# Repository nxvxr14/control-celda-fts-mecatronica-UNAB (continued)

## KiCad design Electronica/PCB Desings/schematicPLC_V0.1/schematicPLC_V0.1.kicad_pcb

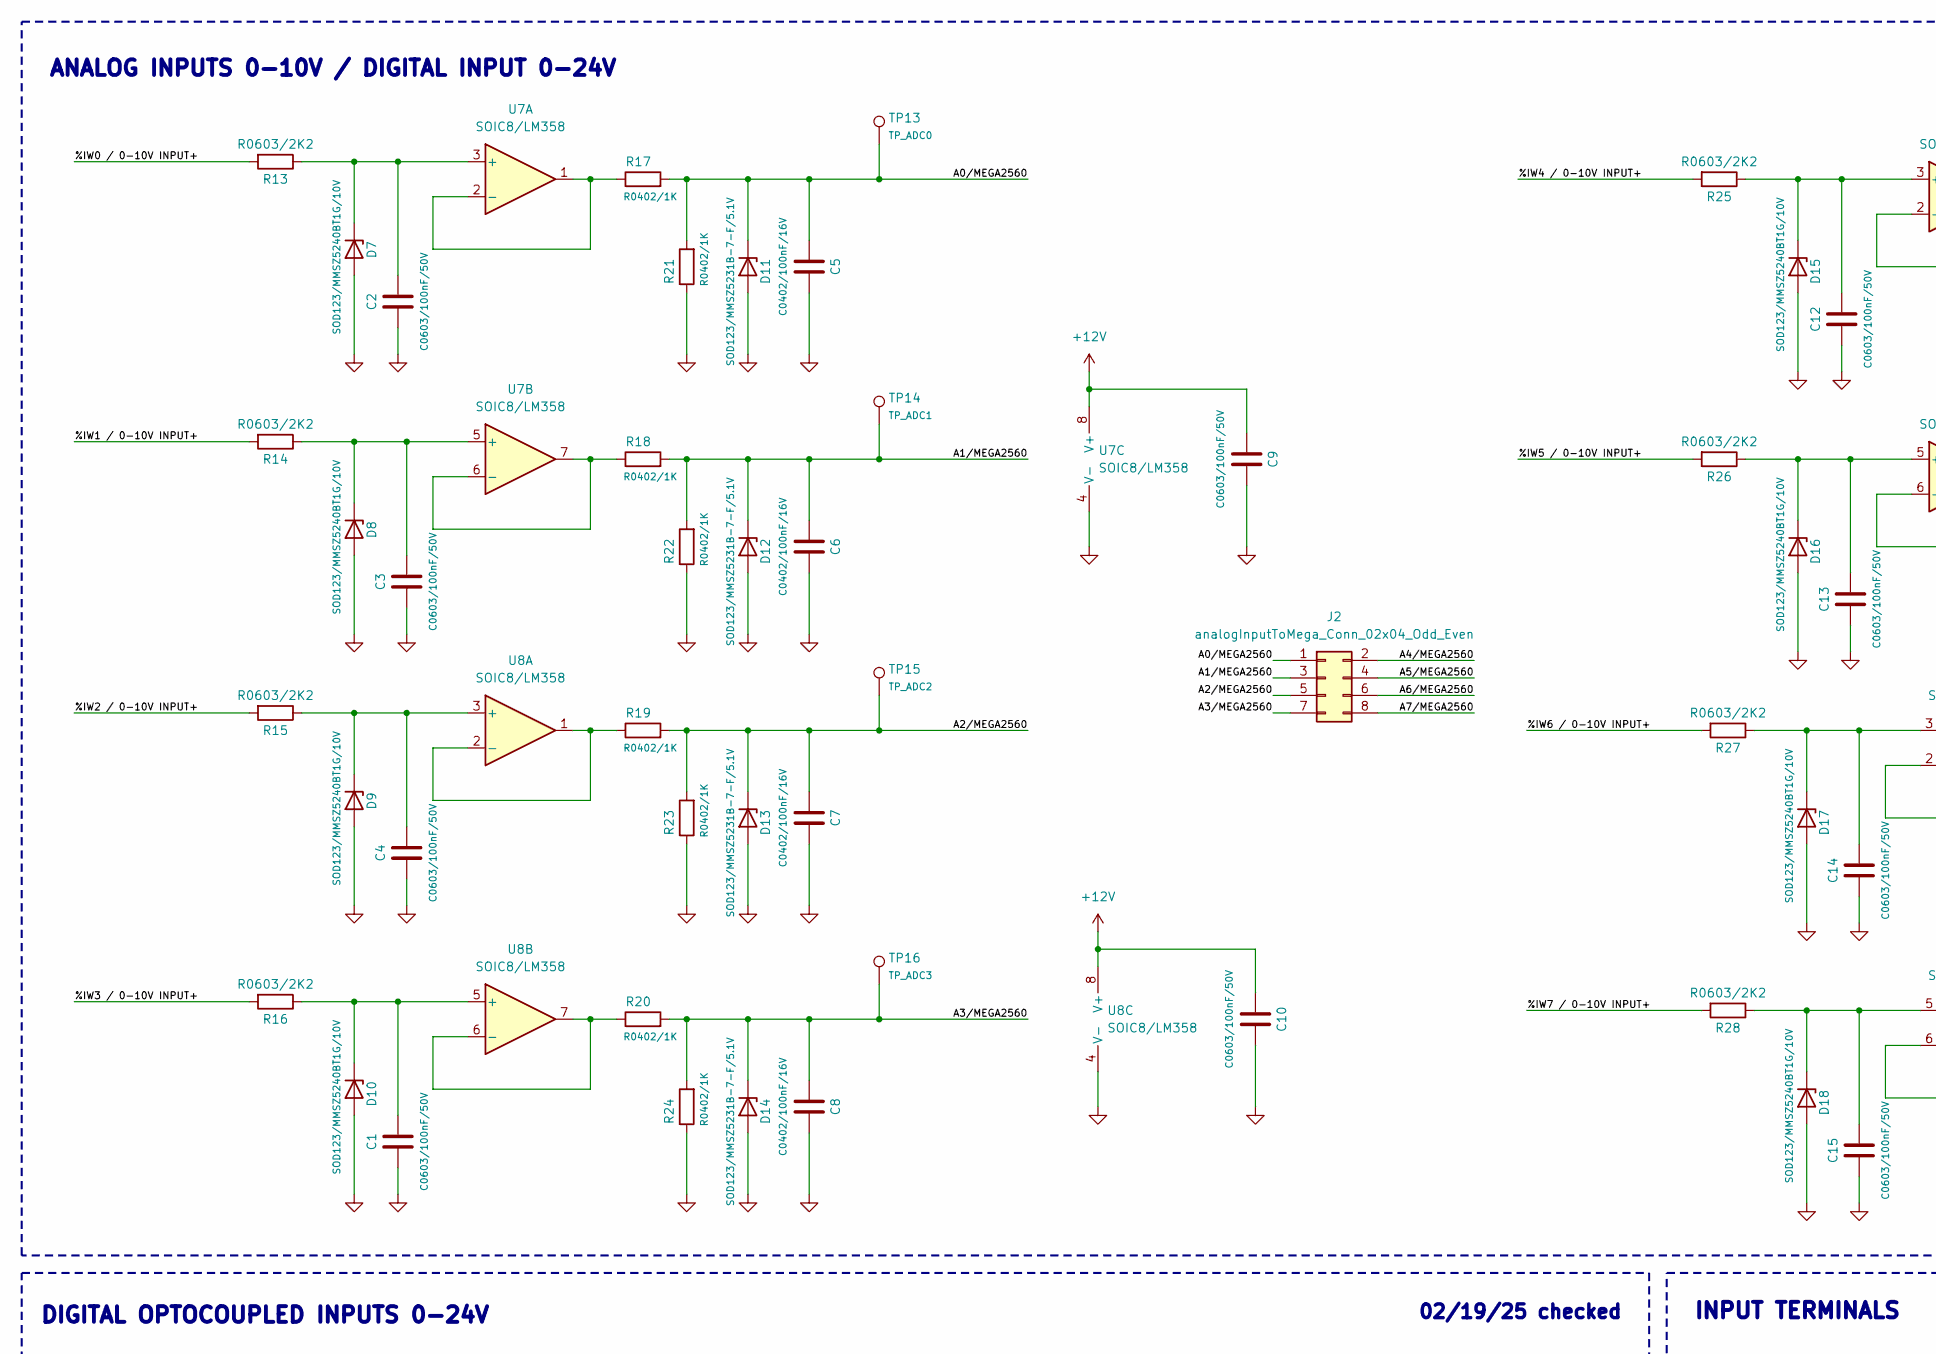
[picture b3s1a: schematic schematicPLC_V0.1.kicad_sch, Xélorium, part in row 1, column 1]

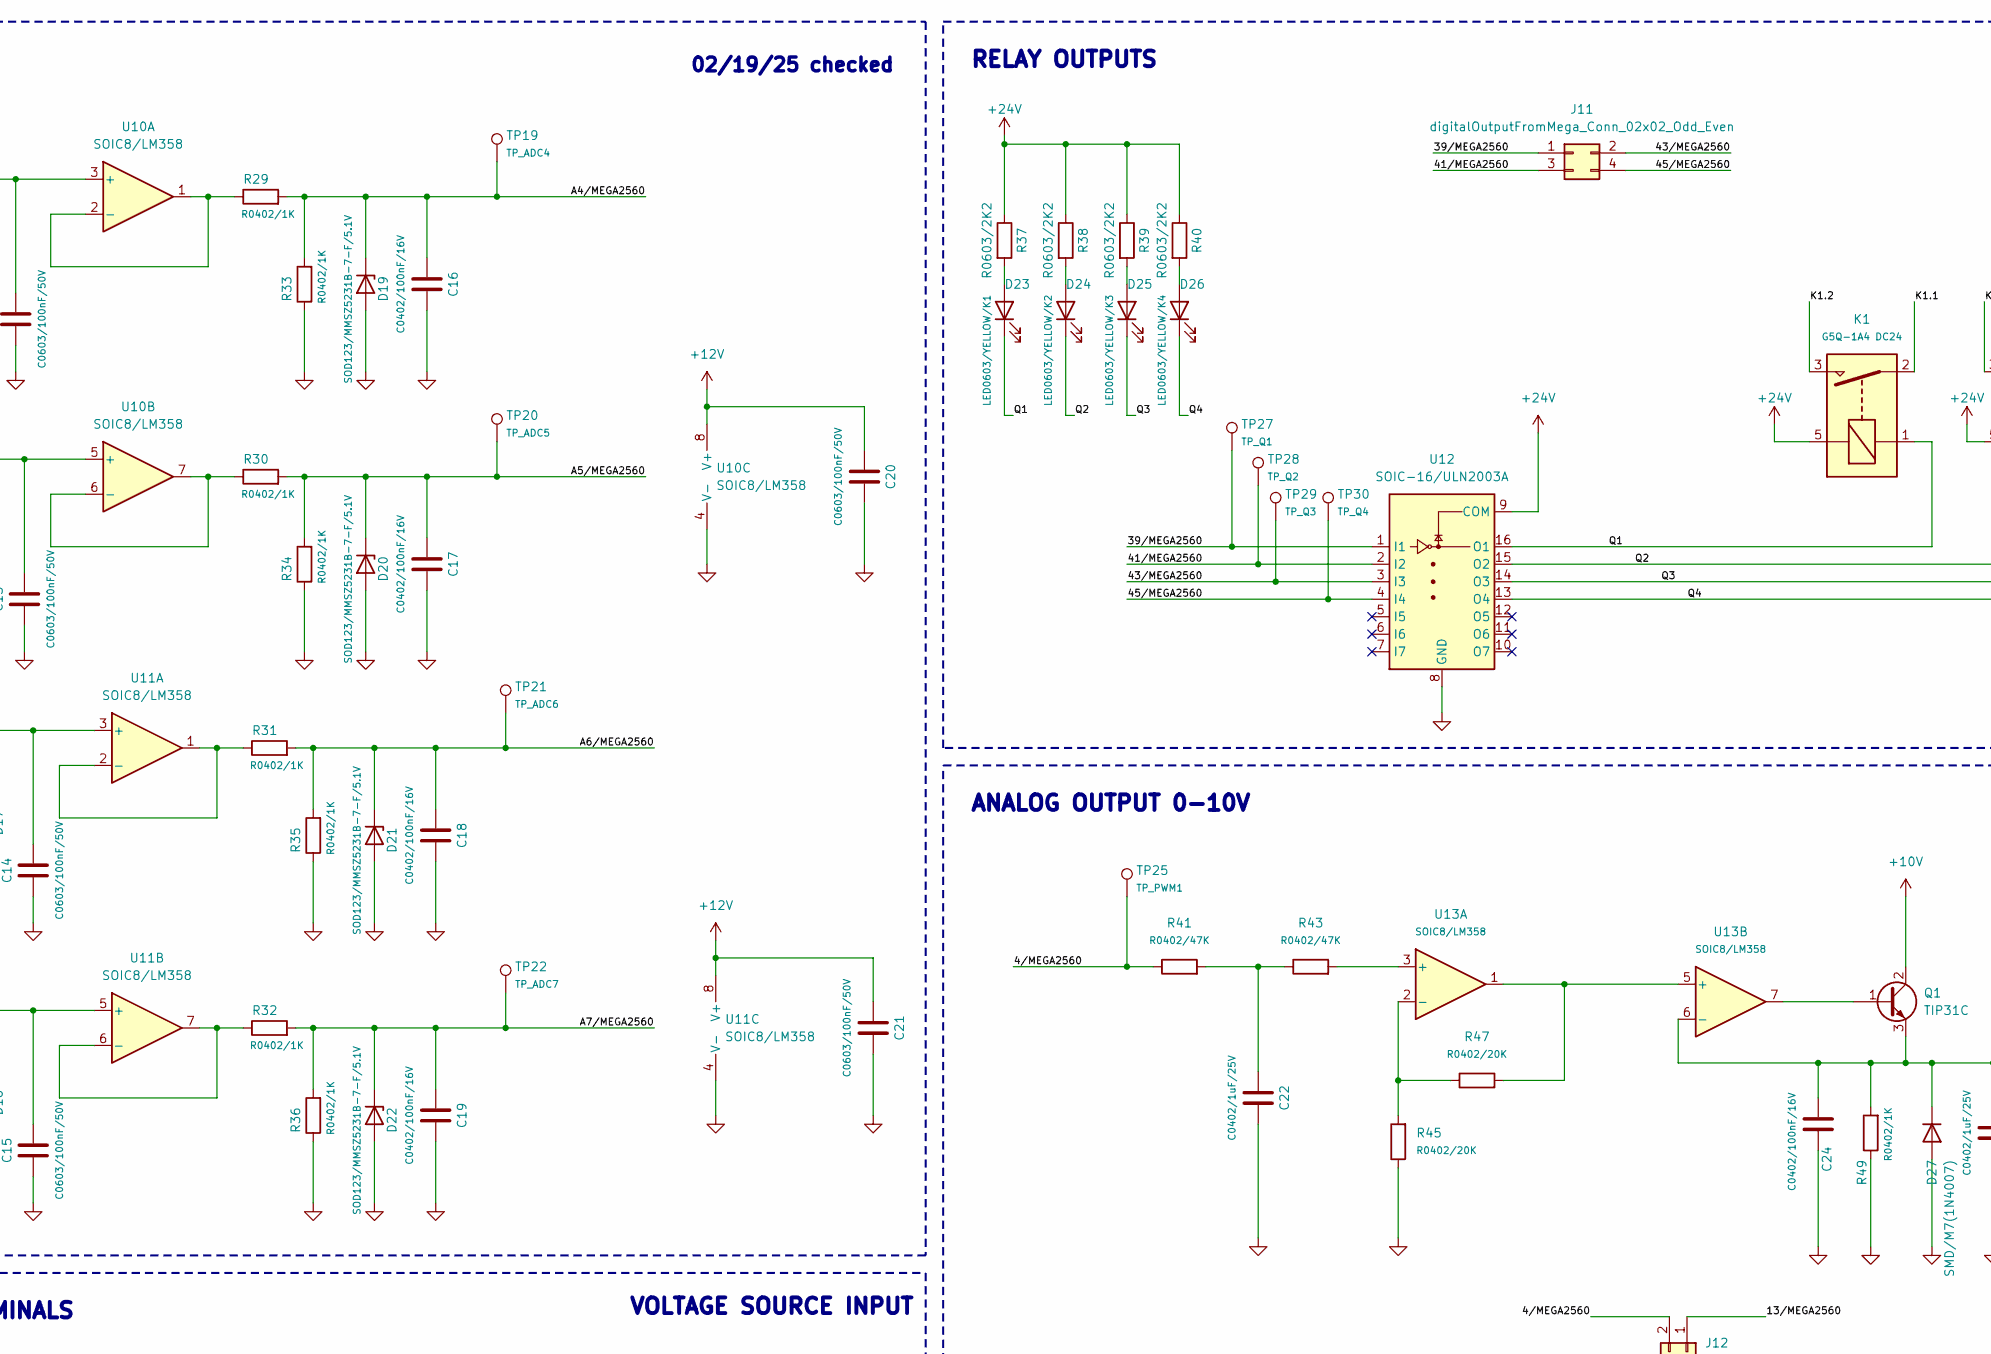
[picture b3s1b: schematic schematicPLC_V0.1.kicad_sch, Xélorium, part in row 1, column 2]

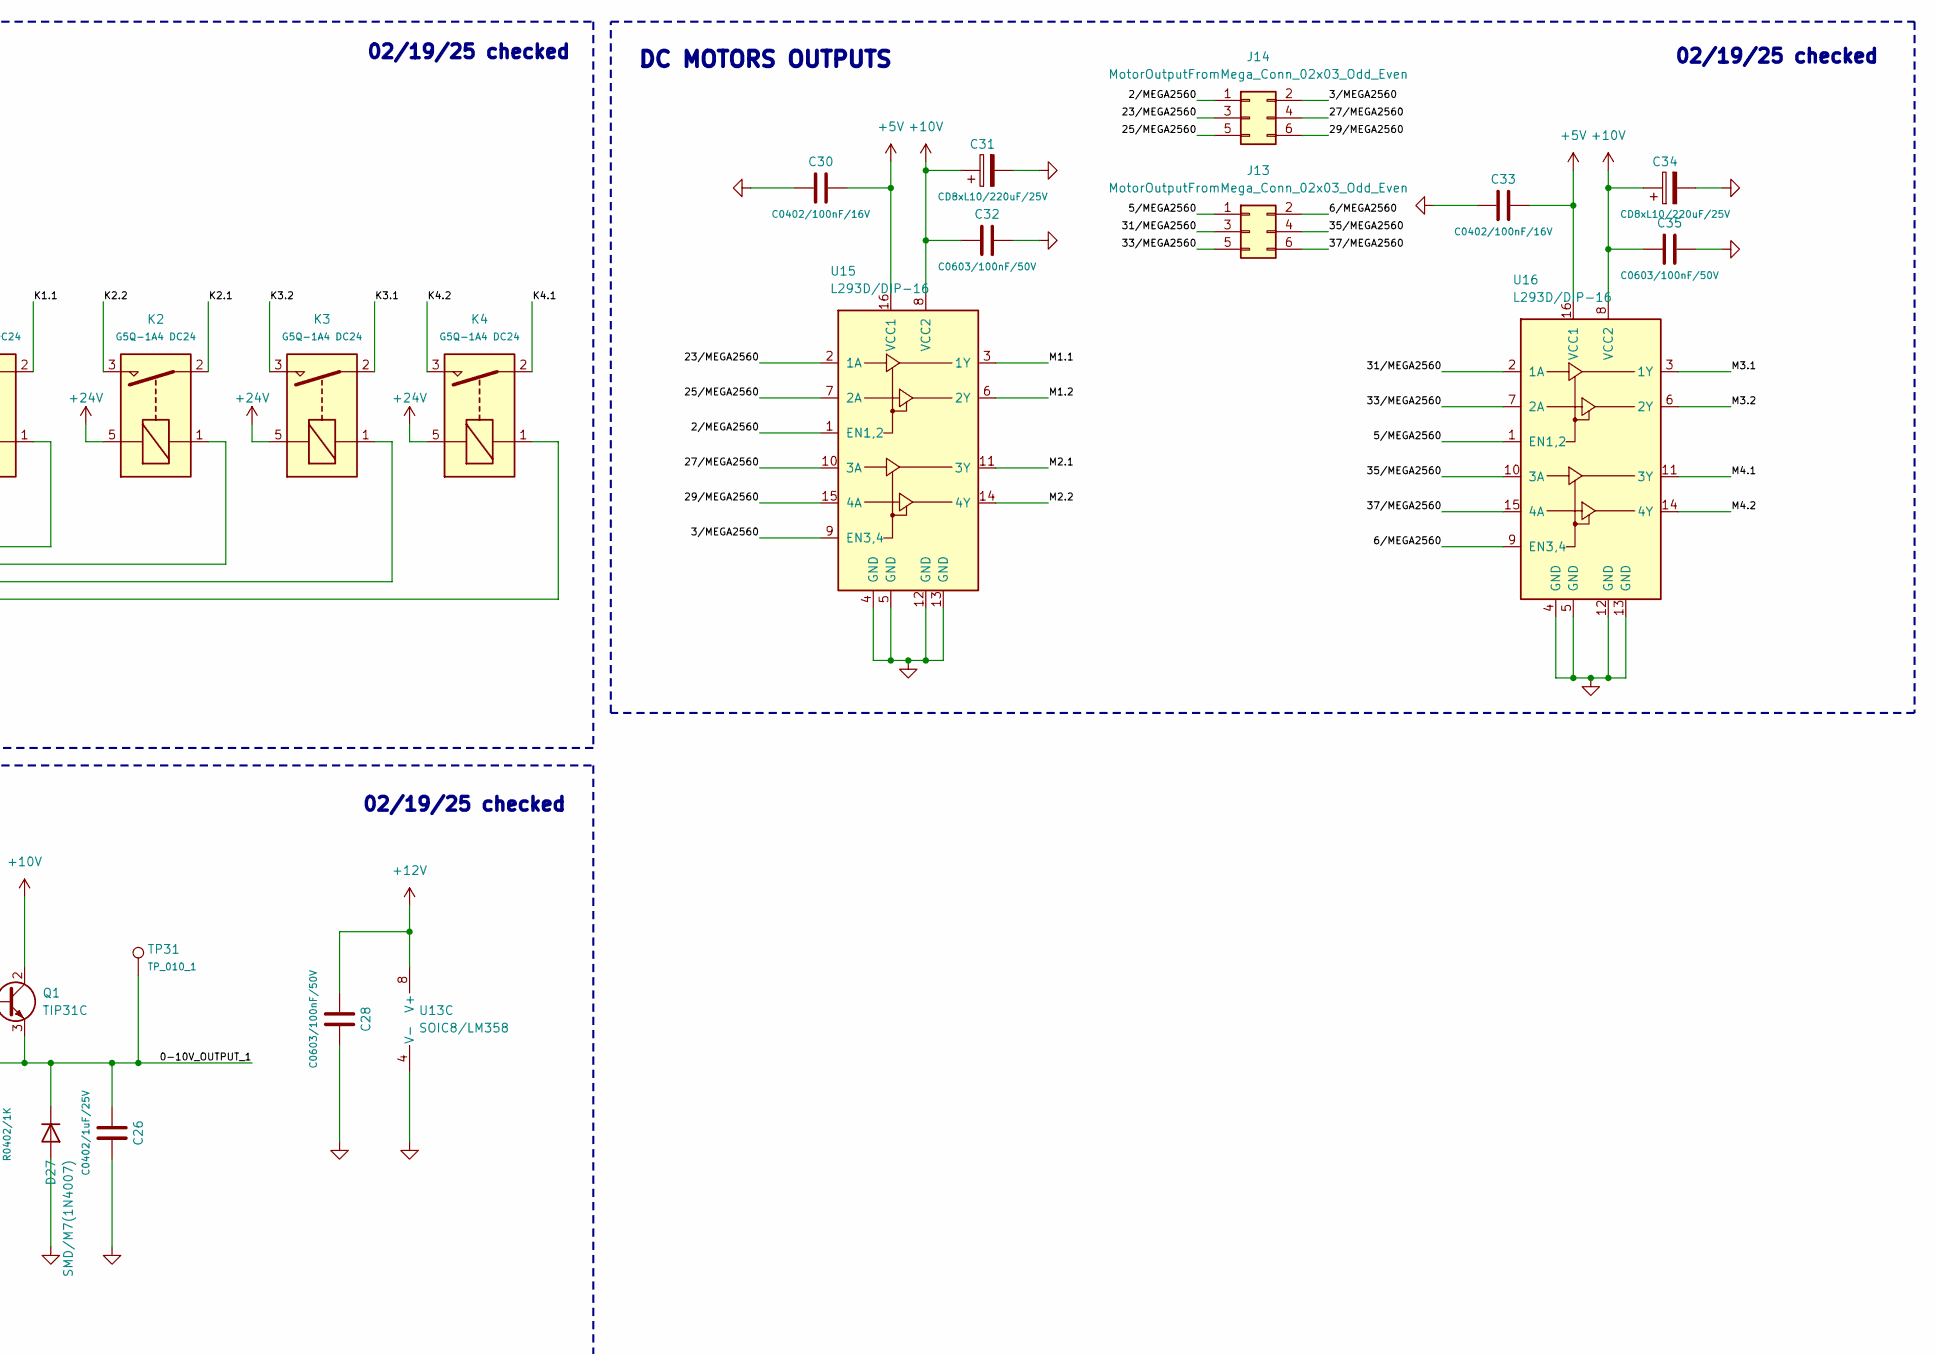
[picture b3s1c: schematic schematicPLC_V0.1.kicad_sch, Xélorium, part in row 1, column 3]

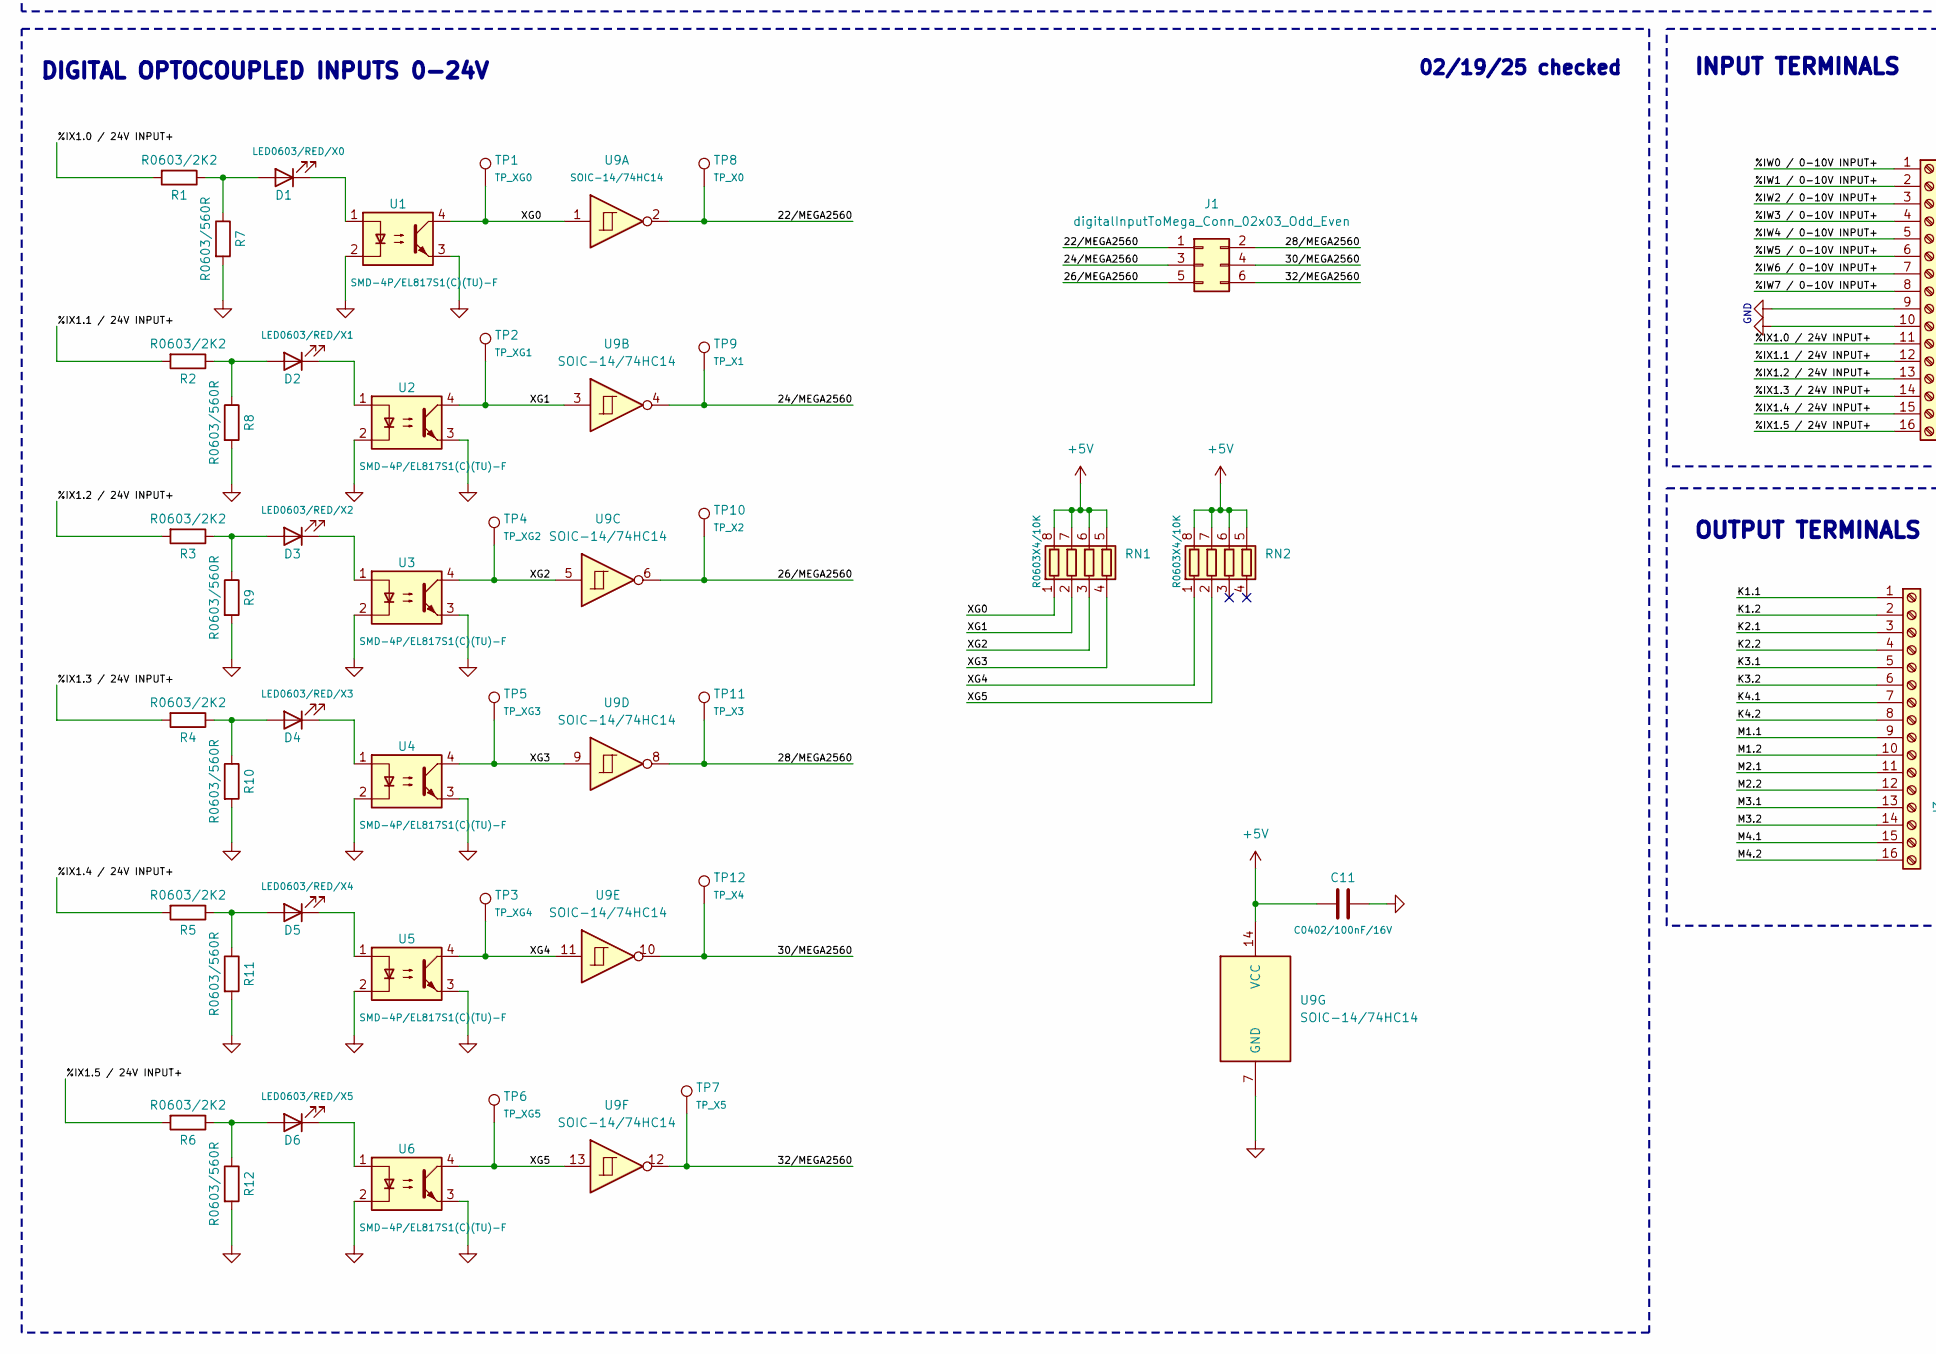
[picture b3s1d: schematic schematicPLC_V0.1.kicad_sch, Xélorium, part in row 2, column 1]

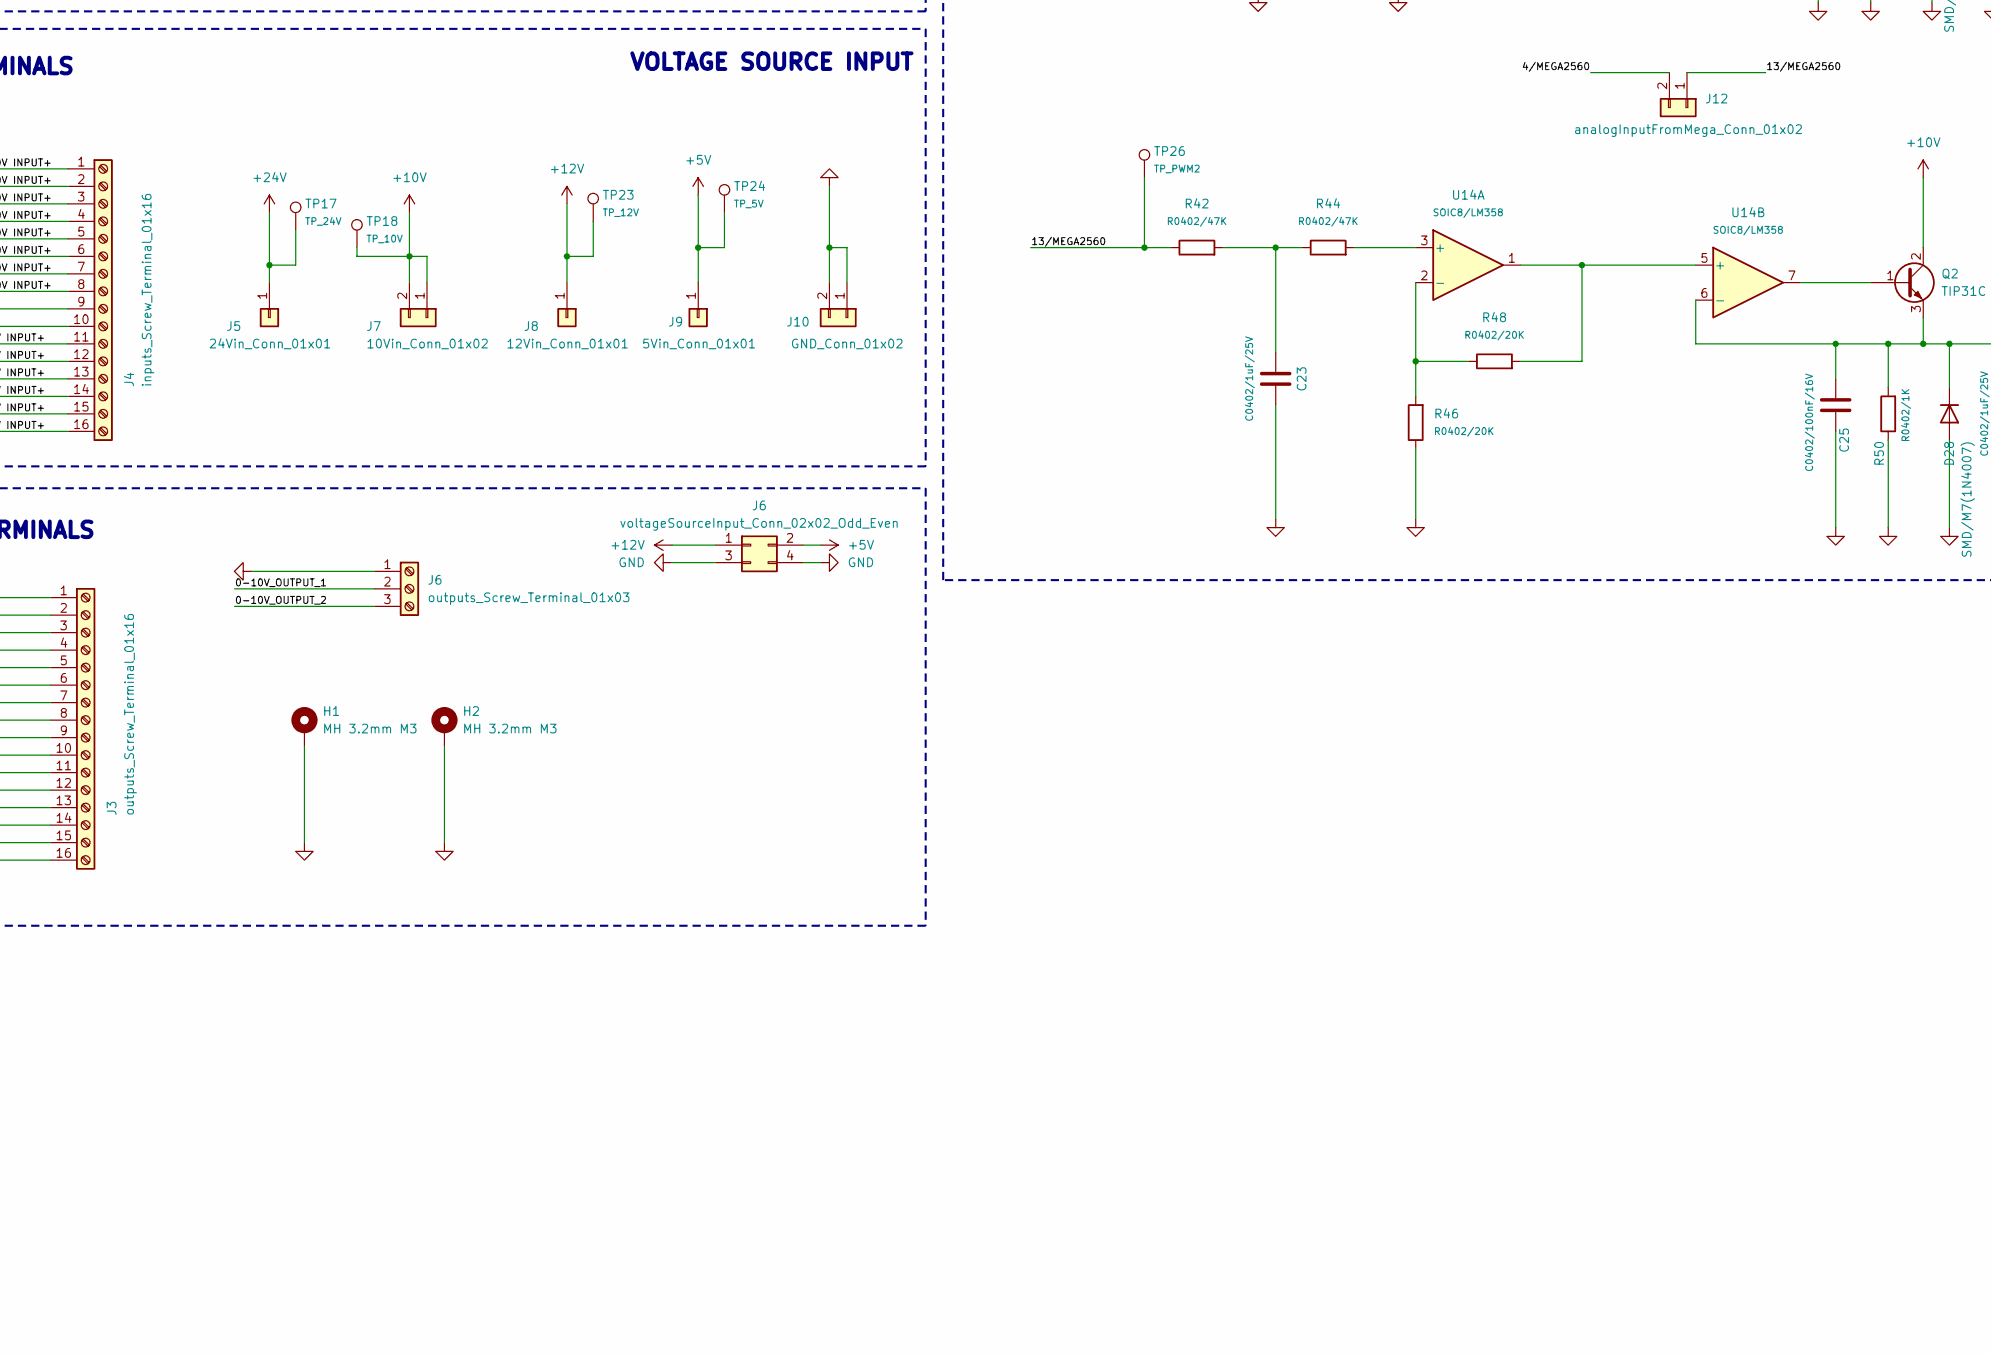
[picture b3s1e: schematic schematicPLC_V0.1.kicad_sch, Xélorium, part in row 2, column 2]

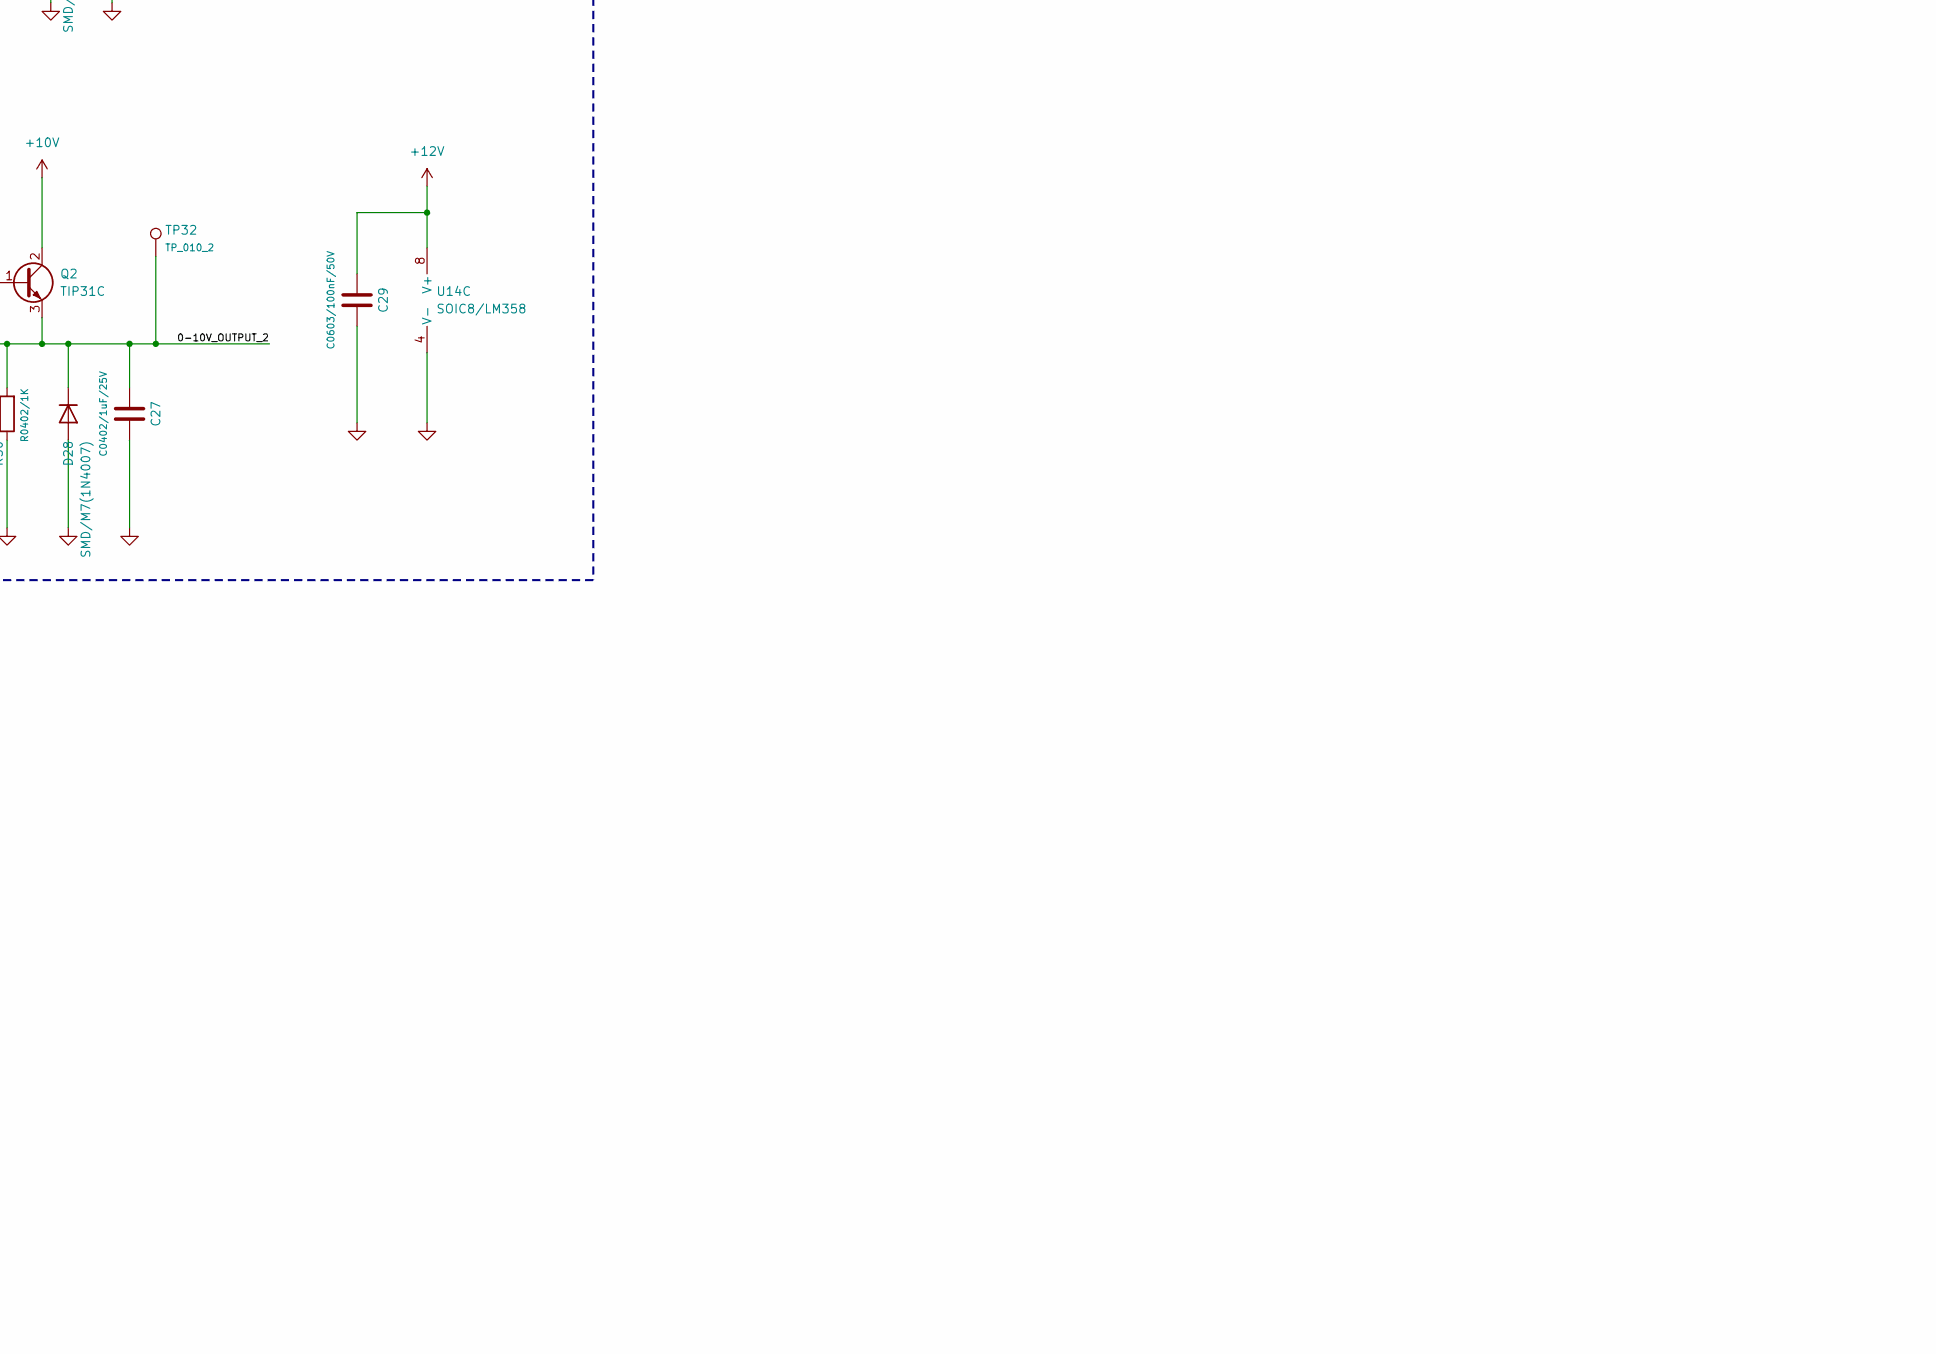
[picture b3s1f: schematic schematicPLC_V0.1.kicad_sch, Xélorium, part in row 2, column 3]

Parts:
C1, C2, C3, C4, C9, C10, C12, C13, C14, C15, C20, C21, C28, C29, C32, C35: C0603/100nF/50V; C_0603_1608Metric; LCSC C14663
C5, C6, C7, C8, C11, C16, C17, C18, C19, C24, C25, C30, C33: C0402/100nF/16V; C_0402_1005Metric; LCSC C1525
C22, C23, C26, C27: C0402/1uF/25V; C_0402_1005Metric; LCSC C52923
C31, C34: CD8xL10/220uF/25V; CP_Elec_8x10; LCSC C178279
D1: LED0603/RED/X0; LED_0603_1608Metric; LCSC C2286
D2: LED0603/RED/X1; LED_0603_1608Metric; LCSC C2286
D3: LED0603/RED/X2; LED_0603_1608Metric; LCSC C2286
D4: LED0603/RED/X3; LED_0603_1608Metric; LCSC C2286
D5: LED0603/RED/X4; LED_0603_1608Metric; LCSC C2286
D6: LED0603/RED/X5; LED_0603_1608Metric; LCSC C2286
D7, D8, D9, D10, D15, D16, D17, D18: SOD123/MMSZ5240BT1G/10V; D_SOD-123; LCSC C82084
D11, D12, D13, D14, D19, D20, D21, D22: SOD123/MMSZ5231B-7-F/5.1V; D_SOD-123; LCSC C85181
D23: LED0603/YELLOW/K1; LED_0603_1608Metric; LCSC C72038
D24: LED0603/YELLOW/K2; LED_0603_1608Metric; LCSC C72038
D25: LED0603/YELLOW/K3; LED_0603_1608Metric; LCSC C72038
D26: LED0603/YELLOW/K4; LED_0603_1608Metric; LCSC C72038
D27, D28: SMD/M7(1N4007); D_SMA; LCSC C95872
H1, H2: MH 3.2mm M3; MountingHole_3.2mm_M3_Pad_Via
J1: digitalInputToMega_Conn_02x03_Odd_Even; PinHeader_2x03_P2.54mm_Vertical
J2: analogInputToMega_Conn_02x04_Odd_Even; PinHeader_2x04_P2.54mm_Vertical
J3: outputs_Screw_Terminal_01x16; TerminalBlock_Phoenix_MKDS-1,5-16_1x16_P5.00mm_Horizontal
J4: inputs_Screw_Terminal_01x16; TerminalBlock_Phoenix_MKDS-1,5-16_1x16_P5.00mm_Horizontal
J5: 24Vin_Conn_01x01; PinSocket_1x01_P2.54mm_Vertical
J6: voltageSourceInput_Conn_02x02_Odd_Even; PinHeader_2x02_P2.54mm_Vertical
J7: 10Vin_Conn_01x02; PinSocket_1x02_P2.54mm_Vertical
J8: 12Vin_Conn_01x01; PinSocket_1x01_P2.54mm_Vertical
J9: 5Vin_Conn_01x01; PinSocket_1x01_P2.54mm_Vertical
J10: GND_Conn_01x02; PinSocket_1x02_P2.54mm_Vertical
J11: digitalOutputFromMega_Conn_02x02_Odd_Even; PinHeader_2x02_P2.54mm_Vertical
J12: analogInputFromMega_Conn_01x02; PinHeader_1x02_P2.54mm_Vertical
J13, J14: MotorOutputFromMega_Conn_02x03_Odd_Even; PinHeader_2x03_P2.54mm_Vertical
K1, K2, K3, K4: G5Q-1A4 DC24; Relay_SPST_Omron-G5Q-1A; LCSC C89311
Q1, Q2: TIP31C; TO-220-3_Vertical; LCSC C963401
R1, R2, R3, R4, R5, R6, R13, R14, R15, R16, R25, R26, R27, R28, R37, R38, R39, R40: R0603/2K2; R_0603_1608Metric; LCSC C4190
R7, R8, R9, R10, R11, R12: R0603/560R; R_0603_1608Metric; LCSC C23204
R17, R18, R19, R20, R21, R22, R23, R24, R29, R30, R31, R32, R33, R34, R35, R36, R49, R50: R0402/1K; R_0402_1005Metric; LCSC C11702
R41, R42, R43, R44: R0402/47K; R_0402_1005Metric; LCSC C25792
R45, R46, R47, R48: R0402/20K; R_0402_1005Metric; LCSC C25765
RN1, RN2: R0603X4/10K; R_Array_Concave_4x0603; LCSC C29718
TP1: TP_XG0; TestPoint_THTPad_D1.0mm_Drill0.5mm
TP2: TP_XG1; TestPoint_THTPad_D1.0mm_Drill0.5mm
TP3: TP_XG4; TestPoint_THTPad_D1.0mm_Drill0.5mm
TP4: TP_XG2; TestPoint_THTPad_D1.0mm_Drill0.5mm
TP5: TP_XG3; TestPoint_THTPad_D1.0mm_Drill0.5mm
TP6: TP_XG5; TestPoint_THTPad_D1.0mm_Drill0.5mm
TP7: TP_X5; TestPoint_THTPad_D1.0mm_Drill0.5mm
TP8: TP_X0; TestPoint_THTPad_D1.0mm_Drill0.5mm
TP9: TP_X1; TestPoint_THTPad_D1.0mm_Drill0.5mm
TP10: TP_X2; TestPoint_THTPad_D1.0mm_Drill0.5mm
TP11: TP_X3; TestPoint_THTPad_D1.0mm_Drill0.5mm
TP12: TP_X4; TestPoint_THTPad_D1.0mm_Drill0.5mm
TP13: TP_ADC0; TestPoint_THTPad_D1.0mm_Drill0.5mm
TP14: TP_ADC1; TestPoint_THTPad_D1.0mm_Drill0.5mm
TP15: TP_ADC2; TestPoint_THTPad_D1.0mm_Drill0.5mm
TP16: TP_ADC3; TestPoint_THTPad_D1.0mm_Drill0.5mm
TP17: TP_24V; TestPoint_THTPad_D1.0mm_Drill0.5mm
TP18: TP_10V; TestPoint_THTPad_D1.0mm_Drill0.5mm
TP19: TP_ADC4; TestPoint_THTPad_D1.0mm_Drill0.5mm
TP20: TP_ADC5; TestPoint_THTPad_D1.0mm_Drill0.5mm
TP21: TP_ADC6; TestPoint_THTPad_D1.0mm_Drill0.5mm
TP22: TP_ADC7; TestPoint_THTPad_D1.0mm_Drill0.5mm
TP23: TP_12V; TestPoint_THTPad_D1.0mm_Drill0.5mm
TP24: TP_5V; TestPoint_THTPad_D1.0mm_Drill0.5mm
TP25: TP_PWM1; TestPoint_THTPad_D1.0mm_Drill0.5mm
TP26: TP_PWM2; TestPoint_THTPad_D1.0mm_Drill0.5mm
TP27: TP_Q1; TestPoint_THTPad_D1.0mm_Drill0.5mm
TP28: TP_Q2; TestPoint_THTPad_D1.0mm_Drill0.5mm
TP29: TP_Q3; TestPoint_THTPad_D1.0mm_Drill0.5mm
TP30: TP_Q4; TestPoint_THTPad_D1.0mm_Drill0.5mm
TP31: TP_010_1; TestPoint_THTPad_D1.0mm_Drill0.5mm
TP32: TP_010_2; TestPoint_THTPad_D1.0mm_Drill0.5mm
U1, U2, U3, U4, U5, U6: SMD-4P/EL817S1(C)(TU)-F; SMDIP-4_W9.53mm; LCSC C106900
U7, U8, U10, U11, U13, U14: SOIC8/LM358; SOIC-8_3.9x4.9mm_P1.27mm; LCSC C7950
U9: SOIC-14/74HC14; SOIC-14_3.9x8.7mm_P1.27mm; LCSC C5605
U12: SOIC-16/ULN2003A; SOIC-16_3.9x9.9mm_P1.27mm; LCSC C7512
U15, U16: L293D/DIP-16; DIP-16_W7.62mm; LCSC C12340

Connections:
+10V: C31.1, C32.1, C34.1, C35.1, J7.1, J7.2, Q1.2 (C), Q2.2 (C), TP18.1, U15.8 (VCC2), U16.8 (VCC2)
+24V: J5.1, K1.5, K2.5, K3.5, K4.5, R37.1, R38.1, R39.1, R40.1, TP17.1, U12.9 (COM)
/2/MEGA2560: J14.1, U15.1 (EN1,2)
/3/MEGA2560: J14.2, U15.9 (EN3,4)
/4/MEGA2560: J12.2, R41.1, TP25.1
/5/MEGA2560: J13.1, U16.1 (EN1,2)
/6/MEGA2560: J13.2, U16.9 (EN3,4)
/13/MEGA2560: J12.1, R42.1, TP26.1
/22/MEGA2560: J1.1, TP8.1, U9.2
/23/MEGA2560: J14.3, U15.2 (1A)
/24/MEGA2560: J1.3, TP9.1, U9.4
/25/MEGA2560: J14.5, U15.7 (2A)
/26/MEGA2560: J1.5, TP10.1, U9.6
/27/MEGA2560: J14.4, U15.10 (3A)
/28/MEGA2560: J1.2, TP11.1, U9.8
/29/MEGA2560: J14.6, U15.15 (4A)
/30/MEGA2560: J1.4, TP12.1, U9.10
/31/MEGA2560: J13.3, U16.2 (1A)
/32/MEGA2560: J1.6, TP7.1, U9.12
/33/MEGA2560: J13.5, U16.7 (2A)
/35/MEGA2560: J13.4, U16.10 (3A)
/37/MEGA2560: J13.6, U16.15 (4A)
/39/MEGA2560: J11.1, TP27.1, U12.1 (I1)
/41/MEGA2560: J11.3, TP28.1, U12.2 (I2)
/43/MEGA2560: J11.2, TP29.1, U12.3 (I3)
/45/MEGA2560: J11.4, TP30.1, U12.4 (I4)
/%IW0 / 0-10V INPUT+: J4.1, R13.2
/%IW1 / 0-10V INPUT+: J4.2, R14.2
/%IW2 / 0-10V INPUT+: J4.3, R15.2
/%IW3 / 0-10V INPUT+: J4.4, R16.2
/%IW4 / 0-10V INPUT+: J4.5, R25.2
/%IW5 / 0-10V INPUT+: J4.6, R26.2
/%IW6 / 0-10V INPUT+: J4.7, R27.2
/%IW7 / 0-10V INPUT+: J4.8, R28.2
/%IX1.0 / 24V INPUT+: J4.11, R1.2
/%IX1.1 / 24V INPUT+: J4.12, R2.2
/%IX1.2 / 24V INPUT+: J4.13, R3.2
/%IX1.3 / 24V INPUT+: J4.14, R4.2
/%IX1.4 / 24V INPUT+: J4.15, R5.2
/%IX1.5 / 24V INPUT+: J4.16, R6.2
/A0/MEGA2560: C5.1, D11.1 (K), J2.1, R17.2, R21.2, TP13.1
/A1/MEGA2560: C6.1, D12.1 (K), J2.3, R18.2, R22.2, TP14.1
/A2/MEGA2560: C7.1, D13.1 (K), J2.5, R19.2, R23.2, TP15.1
/A3/MEGA2560: C8.1, D14.1 (K), J2.7, R20.2, R24.2, TP16.1
/A4/MEGA2560: C16.1, D19.1 (K), J2.2, R29.2, R33.2, TP19.1
/A5/MEGA2560: C17.1, D20.1 (K), J2.4, R30.2, R34.2, TP20.1
/A6/MEGA2560: C18.1, D21.1 (K), J2.6, R31.2, R35.2, TP21.1
/A7/MEGA2560: C19.1, D22.1 (K), J2.8, R32.2, R36.2, TP22.1
/K1.1: J3.1, K1.2
/K1.2: J3.2, K1.3
/K2.1: J3.3, K2.2
/K2.2: J3.4, K2.3
/K3.1: J3.5, K3.2
/K3.2: J3.6, K3.3
/K4.1: J3.7, K4.2
/K4.2: J3.8, K4.3
/M1.1: J3.9, U15.3 (1Y)
/M1.2: J3.10, U15.6 (2Y)
/M2.1: J3.11, U15.11 (3Y)
/M2.2: J3.12, U15.14 (4Y)
/M3.1: J3.13, U16.3 (1Y)
/M3.2: J3.14, U16.6 (2Y)
/M4.1: J3.15, U16.11 (3Y)
/M4.2: J3.16, U16.14 (4Y)
/Q1: D23.1 (K), K1.1, U12.16 (O1)
/Q2: D24.1 (K), K2.1, U12.15 (O2)
/Q3: D25.1 (K), K3.1, U12.14 (O3)
/Q4: D26.1 (K), K4.1, U12.13 (O4)
/XG0: RN1.1 (R1.1), TP1.1, U1.4, U9.1
/XG1: RN1.2 (R2.1), TP2.1, U2.4, U9.3
/XG2: RN1.3 (R3.1), TP4.1, U3.4, U9.5
/XG3: RN1.4 (R4.1), TP5.1, U4.4, U9.9
/XG4: RN2.1 (R1.1), TP3.1, U5.4, U9.11
/XG5: RN2.2 (R2.1), TP6.1, U6.4, U9.13
unnamed: C22.1, R41.2, R43.1
unnamed: C23.1, R42.2, R44.1
unnamed: D1.2 (A), R1.1, R7.1
unnamed: D1.1 (K), U1.1
unnamed: D2.2 (A), R2.1, R8.1
unnamed: D2.1 (K), U2.1
unnamed: D3.2 (A), R3.1, R9.1
unnamed: D3.1 (K), U3.1
unnamed: D4.2 (A), R4.1, R10.1
unnamed: D4.1 (K), U4.1
unnamed: D5.2 (A), R5.1, R11.1
unnamed: D5.1 (K), U5.1
unnamed: D6.2 (A), R6.1, R12.1
unnamed: D6.1 (K), U6.1
unnamed: C2.2, D7.1 (K), R13.1, U7.3 (+)
unnamed: C3.2, D8.1 (K), R14.1, U7.5 (+)
unnamed: C4.2, D9.1 (K), R15.1, U8.3 (+)
unnamed: C1.2, D10.1 (K), R16.1, U8.5 (+)
unnamed: C12.2, D15.1 (K), R25.1, U10.3 (+)
unnamed: C13.2, D16.1 (K), R26.1, U10.5 (+)
unnamed: C14.2, D17.1 (K), R27.1, U11.3 (+)
unnamed: C15.2, D18.1 (K), R28.1, U11.5 (+)
unnamed: D23.2 (A), R37.2
unnamed: D24.2 (A), R38.2
unnamed: D25.2 (A), R39.2
unnamed: D26.2 (A), R40.2
unnamed: Q1.1 (B), U13.7
unnamed: Q2.1 (B), U14.7
unnamed: R17.1, U7.1, U7.2 (-)
unnamed: R18.1, U7.6 (-), U7.7
unnamed: R19.1, U8.1, U8.2 (-)
unnamed: R20.1, U8.6 (-), U8.7
unnamed: R29.1, U10.1, U10.2 (-)
unnamed: R30.1, U10.6 (-), U10.7
unnamed: R31.1, U11.1, U11.2 (-)
unnamed: R32.1, U11.6 (-), U11.7
unnamed: R43.2, U13.3 (+)
unnamed: R45.2, R47.1, U13.2 (-)
unnamed: R47.2, U13.1, U13.5 (+)
unnamed: R44.2, U14.3 (+)
unnamed: R46.2, R48.1, U14.2 (-)
unnamed: R48.2, U14.1, U14.5 (+)

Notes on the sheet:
DIGITAL OPTOCOUPLED INPUTS 0-24V
GND
02/19/25 checked
ANALOG OUTPUT 0-10V
RELAY OUTPUTS
INPUT TERMINALS
ANALOG INPUTS 0-10V / DIGITAL INPUT 0-24V
OUTPUT TERMINALS
DC MOTORS OUTPUTS
VOLTAGE SOURCE INPUT

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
